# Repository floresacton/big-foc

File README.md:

# big-foc
Field Oriented Control Inverter

70V 160A 10kW continuous

12kW peak

99% efficiency at 8kW

48$ BOM + PCB Cost

65x75x32mm size

Ignoring the heatsink, that's 64kW/L :)

## Design Strategy

### 1. Power and Voltage Rating
- **Power Rating**: Target continuous and peak power
- **Battery Voltage**: 12S = 50.4V, 16S = 67.2V
- **Component Voltage Rating**: Components must be rated at >1.5x-2x battery voltage
  - Example: 16S battery (67.2V max) → 100V+ rated components minimum
  - Margin for voltage spikes, ringing
- **Thermal Limitation**: Max accepted power dissipation at continuous and peak power, <=100C

### 2. Power Stage Design

#### Switch Selection by Voltage
- **Low Voltage (<300V)**: MOSFETs
  - Aim for lower RDS(on) better conduction losses
  - Aim for lower total gate charge for better switching losses
  - Most cost-effective (100V rated components very common)
- **High Voltage (>300V)**: SiC FETs or IGBTs
  - SiC FETs: Fast switching, lower losses
  - IGBTs: Slower switching, higher switching losses, very high power

#### Gate Driver Selection
- **Bootstrap Drivers**: 
  - Simple, low cost
  - Requires minimum duty cycle for bootstrap to charge
  - Usually fine until back emf approaches battery voltage
  - Pick a fast reverse recovery charge diode
  
- **Isolated Drivers**:
  - Independent high-side supply
  - Usually for high-voltage (>300V)
  - Can handle 100% duty cycle
  - Expensive, more complex

### 3. Power Loss Analysis (very important)

#### Switching Losses
- Target switching frequency from 20-25khz (non audible range & less harmonic distortion)
- Transformers and motors are inductive loads (different switching waveforms than resistive switching loss)
- Switching loss ~= 1/2\*switching frequency\*current*voltage\*(t_on+t_off)
- t_on, t_off ~= Q_gate/I_charge
- I_charge = gate drive current

#### Conduction Losses
- I^2*R × rds_on (for mosfets)
- rds_on increases with temperature so we can use parallel FETs without runaway (thermals matter too)

### 4. Current Sensing

#### Sensing Approach
- **Phase count**:
  - Measure 2 phases calculate third (more noise)
  - Measure 3 phases and average (less noise, better if fits & symmetry)

- **In-Phase**:
  - Able to measures phase currents regardless of switch state
  - Higher cost, a lot of common mode noise
  - Better current measurements if done properly
  
- **Low-Side (1-3 shunts)**:
  - Cheaper
  - Simpler ground referenced amplifier design
  - Can only sample during low side conduction
  - Use stm32 timer ADC synchronization

#### Shunt Resistors
 - Should be around or slightly below rds_on of FETs
 - Good to have about 50-75mV at full current
 - Select for 20V/V amplifier (INA181A1 super common & cheap)
 - <=50ppm for 100C temp rise scenario
 - Need amplifier right next to shunt
 - Need center VREF amp for negative and positive current
 - Need to choose settling time to 1% better than 95% duty cycle (bootstrap is limiting factor)

#### Magnetic Sensing
- Hall-effect sensing built in packages
- Galvanic isolation included
- Higher cost, useful for very high currents
- Minimal power dissipation

### 5. Thermals

#### Power Dissipation Calculation
 - On average 2 half bridges are conducting fully, one is not conducting
- total switching loss ~= 4\*single switch loss
- gate charge loss is usually quite small compared to switching and resistive losses for 25khz
- total conduction loss ~= 2\*single conduction loss

#### FET Cooling Orientation
- **Top-Side Cooling**: FETs mounted with drain pad facing up
  - More expensive
  - Easier to cool and route
  
- **Bottom-Side Cooling**: FETs with dissipation through PCB
  - Cheaper
  - Easier assembly
  - Harder low inductance loop

#### Thermal Design Process
1. Calculate junction-to-case thermal resistance (datasheet)
2. Add PCB thermal resistance
3. Add heatsink thermal resistance
4. Junction temp = Ambient + (Total losses \* Total thermal resistance)
5. Target <100C but <60C is better

### 6. Protection and Sensing

#### Temperature Monitoring
- NTC thermistor (cheaper than PTC) on heatsink or FETs
- Lower B kind of better like 3400 because more linear over big range
- 10k 3400B ~= 1k at 100C, 30k at 0C

#### Fast Overvoltage Protection
- Hardware comparator for <1µs response time
- Trigger emergency PWM shutdown (stm32 timer break input)
- Threshold = 0.9% or something of voltage rating
- Directly disables gate drivers
- Optional avalanche diode for last resort protection

#### Voltage Measurement
- Resistor divider to ADC with a little bit of filtering
- Per-phase voltage for locking onto back emf for high speed

### 7. Microcontroller Selection

#### STM32G4 Series
**Key Features for FOC:**
- High-resolution timers with dead-time insertion and center aligned PWM
- Fast 12-bit ADCs
- ADC triggering synchronized to PWM for current sampling
- Multiple ADCs for simultaneous phase current sampling
- Math acceleration (FPU, CORDIC) for FOC
- Sufficient for >20kHz control loop

**Typical MCU Choices:**
- STM32G431: Small packages, cost-optimized
- STM32G474: More peripherals, flash, and RAM for complex algorithms

### 8. FOC Control Implementation

#### Control Loop Structure
- Current loop: 10-50kHz (1/10 of switching frequency typical)
- Velocity loop: 1-5kHz
- Position loop: 100-1000Hz

#### Key Considerations
- ADC sampling synchronized to PWM valley/center
- Current reconstruction for low-side shunts
- PI controller tuning based on motor parameters
- Clarke/Park transforms for coordinate conversion
- Space Vector Modulation (SVM) for efficient bus utilization
- Add third harmonic for higher effective bus voltage

### 9. PCB Layout (Very very important)
 - Low inductance switching loop
 - di/dt \* L = voltage induced over drain source
 - Low esr (usually MLCC) caps in low inductance switching loop
 - very rough calc Q_sustain = t_deadtime*I_peak
 - Q_sustain / V_spike = C_switch loop
 - Goal to hit V_spike <1% of V_bus
 - Keep loops as small as possible
 - Shunt amplifier right next to shunt resistor

### 10. Connectors
 - Waterproof, either SD13 series or DT Duetch (orange ones) are common
 - Phase and power wires just shrouded, bolt internally

### 11. Example Calculations (for my inverter)
- **Motor Characteristics**
	- 40uH phase to phase inductance
	- AMKs have 2.5nF inter winding capacitance
	- Couldn't find inter-winding capacitance of mine, but I think its relatively small losses compared to conduction
- [MOSFET loss equations](https://www.ti.com/lit/an/slyt664/slyt664.pdf?ts=1762657470589)
- [Layout and more equations](https://www.infineon.com/assets/row/public/documents/24/42/infineon-designing-an-optimized-half-bridge-dc-dc-converter-with-medium-voltage-coolgan-transistors-applicationnotes-en.pdf)
 - **Losses**
	 - Power 8.4kW at 120A rms current or two phases at 170A
	 - 2 phases on at a time on average (same thing as 3 RMS currents)
	 - parallel rds @ 15V: 0.55mohm at 25C, 0.85mohm at 100C
	 - P_cond_tot = 2\*170\*170\*0.00055 = 32W
	 - P_shunt = 2\*170\*170\*0.00033 = 19W
	 - Q_gs2 = 20nC, Q_gd = 50nC, Q_eff = 70nC
	 - Q_actual = 140nC cause parallel FETs
	 - P_sw = 2\*70V\*170A\*25khz\*140nC/4A = 20.8W
	 - P_sw_total = 8.925W\*2 half bridge = 41.6W
     - P_recovery = 25khz\*200nC\*70V*8FETs = 2.8W
	 - P_coss = 12FETs \* 25khz \* 70V^2 \* 2.3nF = 3.4W
	 - P_winding_cap = 3 phase \* 25khz \* 70V^2 \* 2.5nF = 0.9W
	 - P_gate_total = 12 FETs\*250nC\*15V\*25khz = 1.1W
	 - P_gate_drive = <1W
	 - Deadtime 150ns
	 - P_diode = ~1.5\*1.2V\*170A\*25khz\*150ns = 1.2W (a bit sus math but reasonable)
	 - 4% dissipation factor for 1206 2.2uF ~ 10mohm I think for equivalent 10 (randomish number)
	 - Sw_energy = 70V\*170A\*140nC/4A = 0.4mJ per phase
	 - C_droop ~= 0.4mJ/(20uF \* 70V) = 0.3V
	 - The Vrms of the droop is prob below ~50mV
	 - P_cap_sw = 50mV^2/10mohm = 0.25W*3phases comes to <1W
	 - I_ripple ~= 110A
	 - Assuming 70A into ceramics and 40A into electrolytic
	 - 80 ceramics / 70A = 0.87A per ceramic
	 - P_ripple_cer = 0.875^2 \* 100mohm = 80mW
	 - P_cer_tot = 0.08*80 = 6.4W
	 - Electrolytic 3mohm at 25khz (susish think ok)
	 - I_elec ~= 40A/10 = 4A
	 - P_elec = 4A^2 \* 3mohm = 48mW
	 - P_elec_tot = 48mW \* 10 = 0.5W
	 - Total at 8.4kW = 32+41.6+1.1+1.2+1+1+6.4+0.5+3.4+19+2.8= 109.9W
	 - About 98.6% efficiency
- **Control**
	- Max phase current 220A, 210A max (170rms) is 12kW
	- SVPWM
	- Optional 3rd harmonic overmodulation
	- I_phase_rms = I_phase_pk / sqrt(12)
	- I_pk_pk_ripple = 70V / (2 \* 40uH \* 25khz) \* D \* (1-D) = 8.75A ; D=0.5
	- I_pk = 4.4A
	- I_rms = I_pk_pk_ripple / sqrt(12) = 2.5A

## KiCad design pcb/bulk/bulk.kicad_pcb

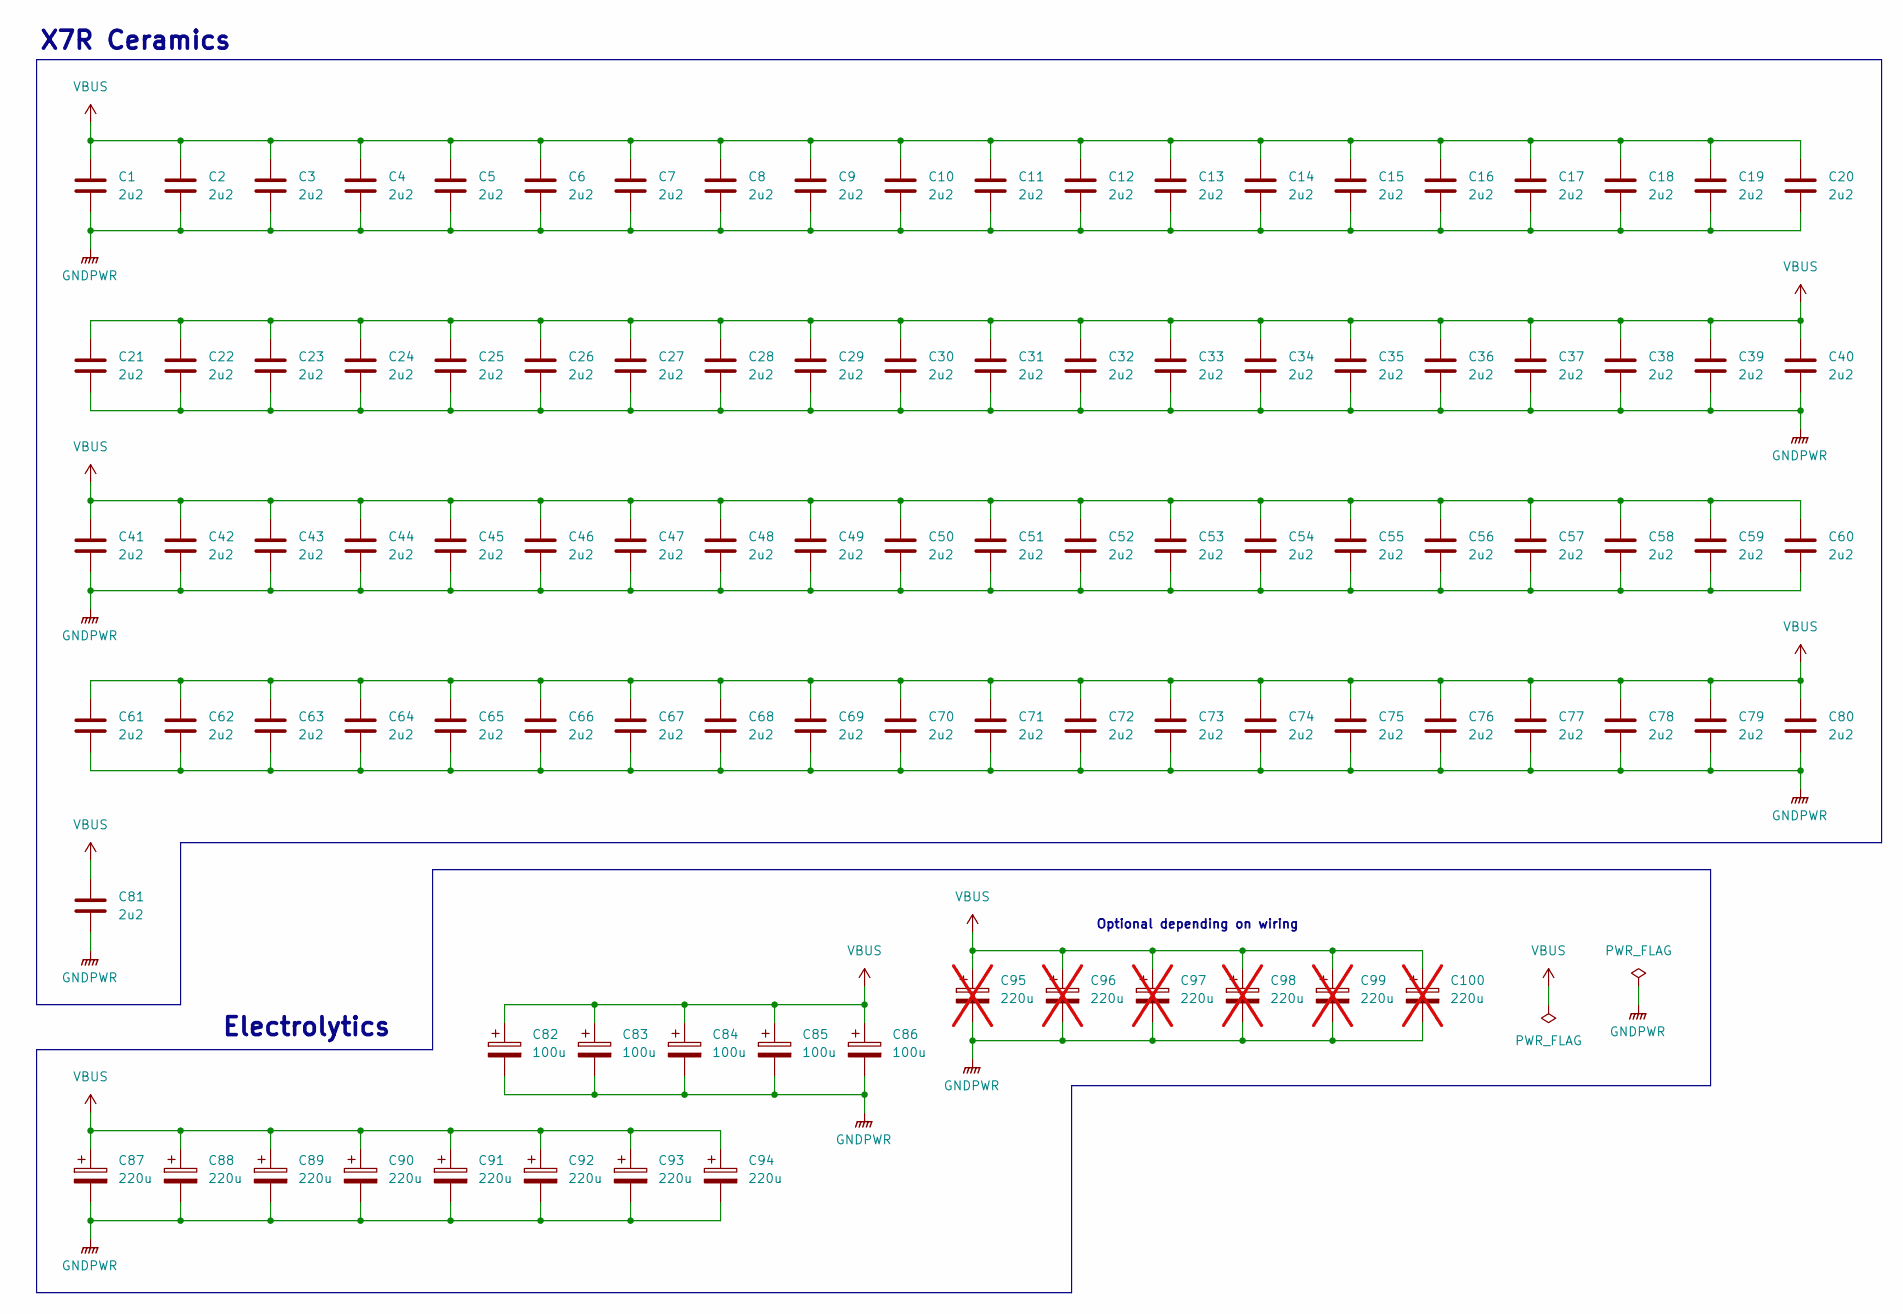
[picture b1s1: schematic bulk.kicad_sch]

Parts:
C1, C2, C3, C4, C5, C6, C7, C8, C9, C10, C11, C12, C13, C14, C15, C16, C17, C18, C19, C20, C21, C22, C23, C24, C25, C26, C27, C28, C29, C30, C31, C32, C33, C34, C35, C36, C37, C38, C39, C40, C41, C42, C43, C44, C45, C46, C47, C48, C49, C50, C51, C52, C53, C54, C55, C56, C57, C58, C59, C60, C61, C62, C63, C64, C65, C66, C67, C68, C69, C70, C71, C72, C73, C74, C75, C76, C77, C78, C79, C80, C81: 2u2; C_1206_3216Metric; LCSC C920964
C82, C83, C84, C85, C86: 100u; C_Radial_D10.0mm_H20.0mm_P5.00mm; LCSC C106541
C87, C88, C89, C90, C91, C92, C93, C94: 220u; C_Radial_D12.5mm_H20.0mm_P5.00mm; LCSC C5213780
C95, C96, C97, C98, C99, C100: 220u; C_Radial_D12.5mm_H20.0mm_P5.00mm; LCSC C5213780; not fitted

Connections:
GNDPWR: C1.2, C2.2, C3.2, C4.2, C5.2, C6.2, C7.2, C8.2, C9.2, C10.2, C11.2, C12.2, C13.2, C14.2, C15.2, C16.2, C17.2, C18.2, C19.2, C20.2, C21.2, C22.2, C23.2, C24.2, C25.2, C26.2, C27.2, C28.2, C29.2, C30.2, C31.2, C32.2, C33.2, C34.2, C35.2, C36.2, C37.2, C38.2, C39.2, C40.2, C41.2, C42.2, C43.2, C44.2, C45.2, C46.2, C47.2, C48.2, C49.2, C50.2, C51.2, C52.2, C53.2, C54.2, C55.2, C56.2, C57.2, C58.2, C59.2, C60.2, C61.2, C62.2, C63.2, C64.2, C65.2, C66.2, C67.2, C68.2, C69.2, C70.2, C71.2, C72.2, C73.2, C74.2, C75.2, C76.2, C77.2, C78.2, C79.2, C80.2, C81.2, C82.2, C83.2, C84.2, C85.2, C86.2, C87.2, C88.2, C89.2, C90.2, C91.2, C92.2, C93.2, C94.2, C95.2, C96.2, C97.2, C98.2, C99.2, C100.2
VBUS: C1.1, C2.1, C3.1, C4.1, C5.1, C6.1, C7.1, C8.1, C9.1, C10.1, C11.1, C12.1, C13.1, C14.1, C15.1, C16.1, C17.1, C18.1, C19.1, C20.1, C21.1, C22.1, C23.1, C24.1, C25.1, C26.1, C27.1, C28.1, C29.1, C30.1, C31.1, C32.1, C33.1, C34.1, C35.1, C36.1, C37.1, C38.1, C39.1, C40.1, C41.1, C42.1, C43.1, C44.1, C45.1, C46.1, C47.1, C48.1, C49.1, C50.1, C51.1, C52.1, C53.1, C54.1, C55.1, C56.1, C57.1, C58.1, C59.1, C60.1, C61.1, C62.1, C63.1, C64.1, C65.1, C66.1, C67.1, C68.1, C69.1, C70.1, C71.1, C72.1, C73.1, C74.1, C75.1, C76.1, C77.1, C78.1, C79.1, C80.1, C81.1, C82.1, C83.1, C84.1, C85.1, C86.1, C87.1, C88.1, C89.1, C90.1, C91.1, C92.1, C93.1, C94.1, C95.1, C96.1, C97.1, C98.1, C99.1, C100.1

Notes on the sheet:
X7R Ceramics
Optional depending on wiring
Electrolytics

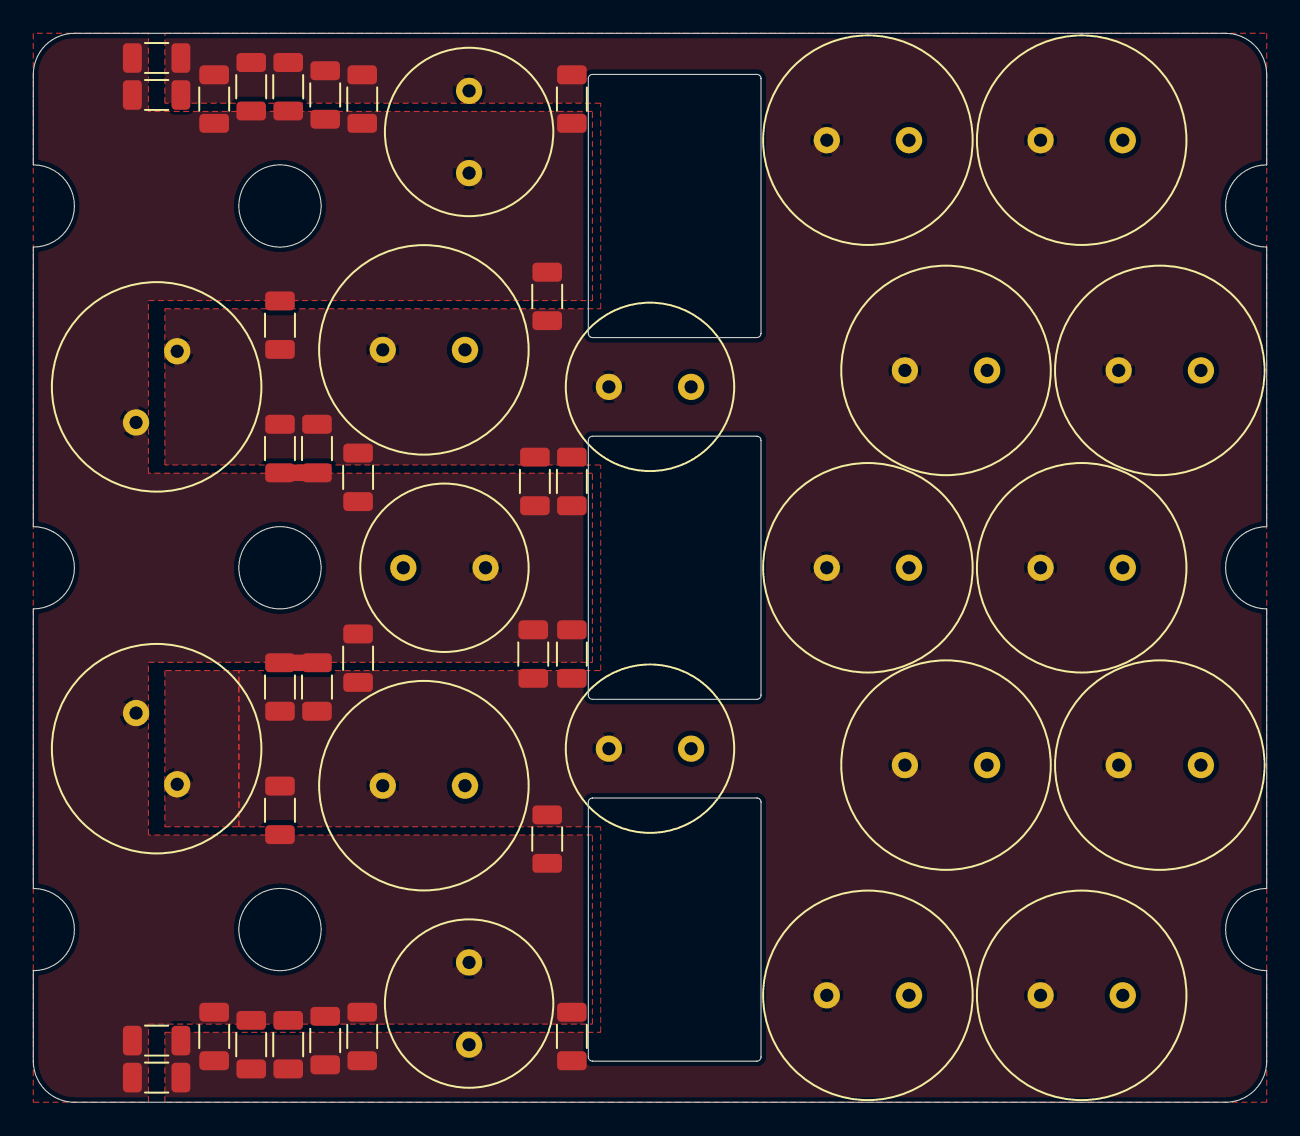
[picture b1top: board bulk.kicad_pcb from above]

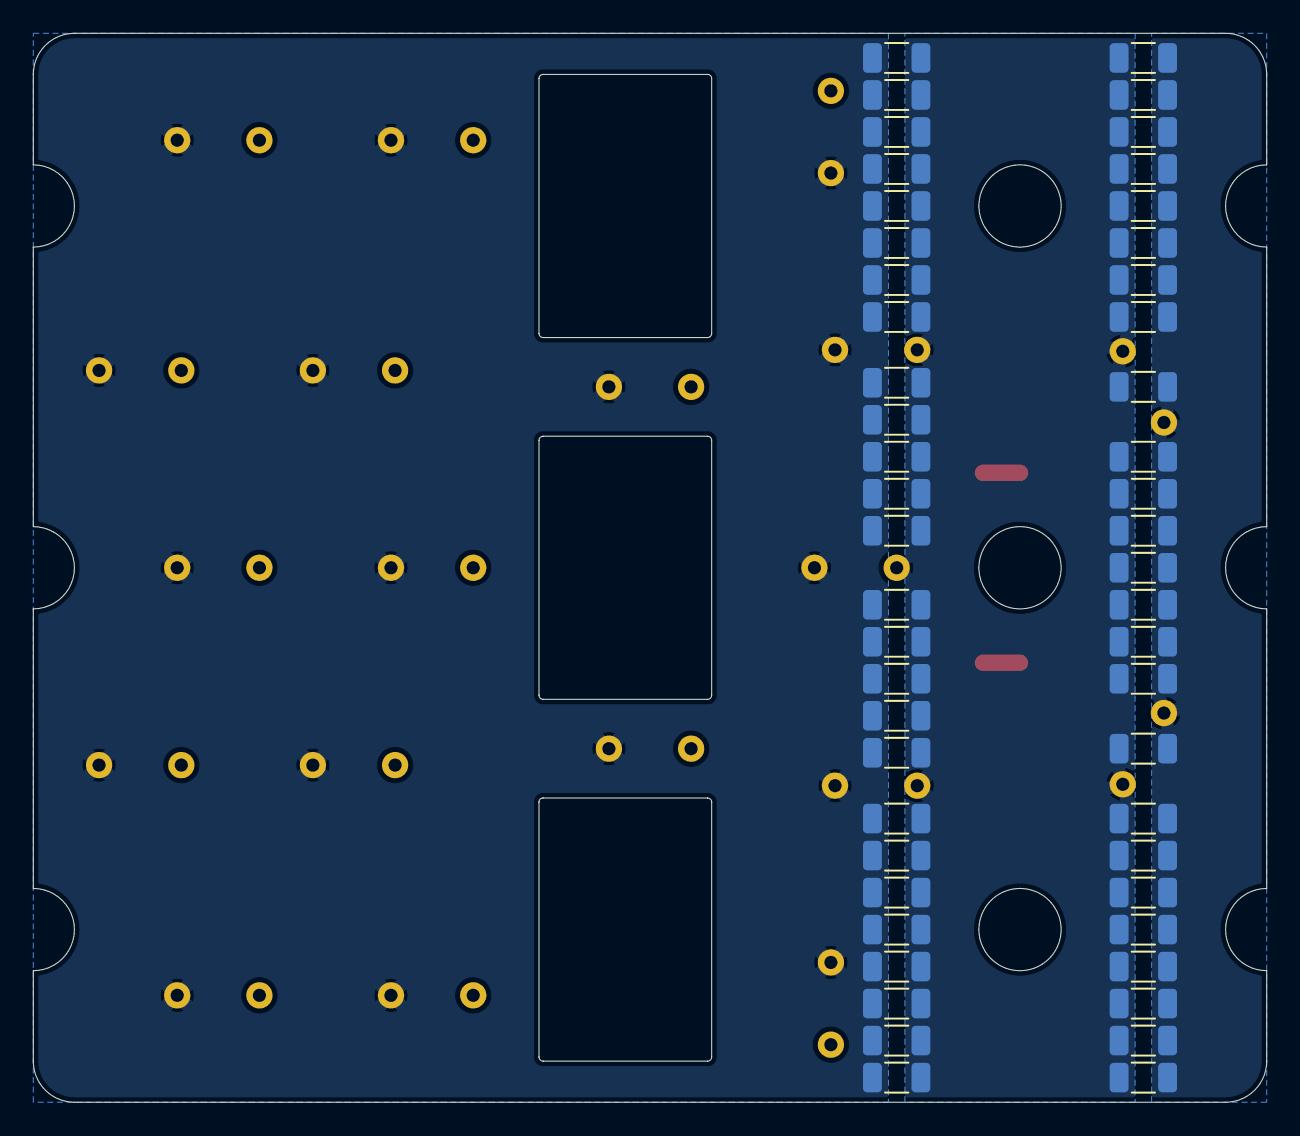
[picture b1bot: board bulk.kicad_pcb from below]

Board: 2 copper layers, 75.0 x 65.0 mm, 100 parts (51 on the bottom side), 2 nets.

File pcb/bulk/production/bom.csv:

Designator,Footprint,Quantity,Value,LCSC Part #
"C1, C10, C11, C12, C13, C14, C15, C16, C17, C18, C19, C2, C20, C21, C22, C23, C24, C25, C26, C27, C28, C29, C3, C30, C31, C32, C33, C34, C35, C36, C37, C38, C39, C4, C40, C41, C42, C43, C44, C45, C46, C47, C48, C49, C5, C50, C51, C52, C53, C54, C55, C56, C57, C58, C59, C6, C60, C61, C62, C63, C64, C65, C66, C67, C68, C69, C7, C70, C71, C72, C73, C74, C75, C76, C77, C78, C79, C8, C80, C81, C9",1206,81,2u2,C920964
"C82, C83, C84, C85, C86",C_Radial_D10.0mm_H20.0mm_P5.00mm,5,100u,C106541
"C87, C88, C89, C90, C91, C92, C93, C94",C_Radial_D12.5mm_H20.0mm_P5.00mm,8,220u,C5213780

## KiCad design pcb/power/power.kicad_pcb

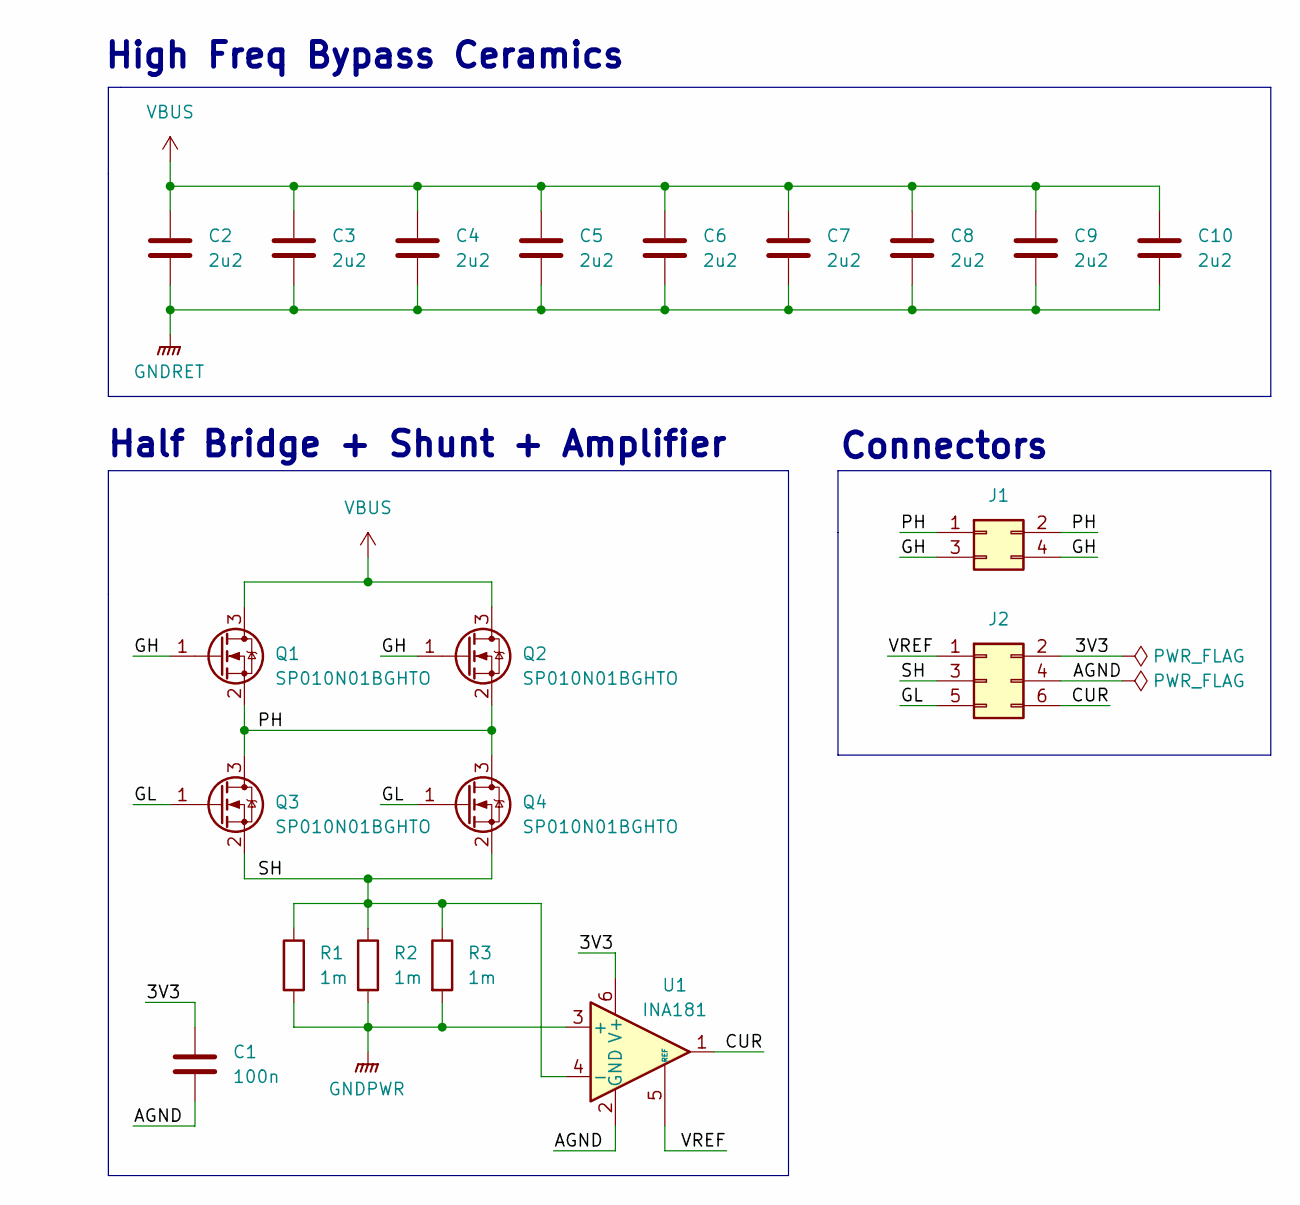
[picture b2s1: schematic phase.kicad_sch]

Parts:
C1: 100n; C_0402_1005Metric; LCSC C307331
C2, C3, C4, C5, C6, C7, C8, C9, C10: 2u2; C_1206_3216Metric; LCSC C920964
J1: Conn_02x02_Odd_Even; PinHeader_2x02_P1.27mm_Vertical_SMD; LCSC C27985143
J2: Conn_02x03_Odd_Even; PinHeader_2x03_P1.27mm_Vertical_SMD; LCSC C27985144
Q1, Q2, Q3, Q4: SP010N01BGHTO; Infineon_PG-HSOF-8-1; LCSC C22385350
R1, R2, R3: 1m; R_Shunt_3921; LCSC C2927603
U1: INA181; SOT-23-6; LCSC C52097916

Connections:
/Phase1/3V3: C1.1, J2.2, U1.6 (V+)
/Phase1/AGND: C1.2, J2.4, U1.2 (GND)
/Phase1/CUR: J2.6, U1.1
/Phase1/GH: J1.3, J1.4, Q1.1 (G), Q2.1 (G)
/Phase1/GL: J2.5, Q3.1 (G), Q4.1 (G)
/Phase1/PH: J1.1, J1.2, Q1.2 (S), Q2.2 (S), Q3.3 (D), Q4.3 (D)
/Phase1/SH: J2.3, Q3.2 (S), Q4.2 (S), R1.1, R2.1, R3.1, U1.4 (-)
/Phase1/VREF: J2.1, U1.5 (REF)
GNDPWR: R1.2, R2.2, R3.2, U1.3 (+); also elsewhere on the board
GNDRET: C2.2, C3.2, C4.2, C5.2, C6.2, C7.2, C8.2, C9.2, C10.2; also elsewhere on the board
VBUS: C2.1, C3.1, C4.1, C5.1, C6.1, C7.1, C8.1, C9.1, C10.1, Q1.3 (D), Q2.3 (D); also elsewhere on the board

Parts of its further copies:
C11, C21: 100n; C_0402_1005Metric; LCSC C307331
C12, C13, C14, C15, C16, C17, C18, C19, C20, C22, C23, C24, C25, C26, C27, C28, C29, C30: 2u2; C_1206_3216Metric; LCSC C920964
J3, J5: Conn_02x02_Odd_Even; PinHeader_2x02_P1.27mm_Vertical_SMD; LCSC C27985143
J4, J6: Conn_02x03_Odd_Even; PinHeader_2x03_P1.27mm_Vertical_SMD; LCSC C27985144
Q5, Q6, Q7, Q8, Q9, Q10, Q11, Q12: SP010N01BGHTO; Infineon_PG-HSOF-8-1; LCSC C22385350
R4, R5, R6, R7, R8, R9: 1m; R_Shunt_3921; LCSC C2927603
U2, U3: INA181; SOT-23-6; LCSC C52097916

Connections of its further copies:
/Phase2/3V3: C11.1, J4.2, U2.6 (V+)
/Phase2/AGND: C11.2, J4.4, U2.2 (GND)
/Phase2/CUR: J4.6, U2.1
/Phase2/GH: J3.3, J3.4, Q5.1 (G), Q6.1 (G)
/Phase2/GL: J4.5, Q7.1 (G), Q8.1 (G)
/Phase2/PH: J3.1, J3.2, Q5.2 (S), Q6.2 (S), Q7.3 (D), Q8.3 (D)
/Phase2/SH: J4.3, Q7.2 (S), Q8.2 (S), R4.1, R5.1, R6.1, U2.4 (-)
/Phase2/VREF: J4.1, U2.5 (REF)
/Phase3/3V3: C21.1, J6.2, U3.6 (V+)
/Phase3/AGND: C21.2, J6.4, U3.2 (GND)
/Phase3/CUR: J6.6, U3.1
/Phase3/GH: J5.3, J5.4, Q9.1 (G), Q10.1 (G)
/Phase3/GL: J6.5, Q11.1 (G), Q12.1 (G)
/Phase3/PH: J5.1, J5.2, Q9.2 (S), Q10.2 (S), Q11.3 (D), Q12.3 (D)
/Phase3/SH: J6.3, Q11.2 (S), Q12.2 (S), R7.1, R8.1, R9.1, U3.4 (-)
/Phase3/VREF: J6.1, U3.5 (REF)
GNDPWR: R4.2, R5.2, R6.2, R7.2, R8.2, R9.2, U2.3 (+), U3.3 (+); also elsewhere on the board
GNDRET: C12.2, C13.2, C14.2, C15.2, C16.2, C17.2, C18.2, C19.2, C20.2, C22.2, C23.2, C24.2, C25.2, C26.2, C27.2, C28.2, C29.2, C30.2; also elsewhere on the board
VBUS: C12.1, C13.1, C14.1, C15.1, C16.1, C17.1, C18.1, C19.1, C20.1, C22.1, C23.1, C24.1, C25.1, C26.1, C27.1, C28.1, C29.1, C30.1, Q5.3 (D), Q6.3 (D), Q9.3 (D), Q10.3 (D); also elsewhere on the board

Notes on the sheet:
High Freq Bypass Ceramics
Connectors
Half Bridge + Shunt + Amplifier

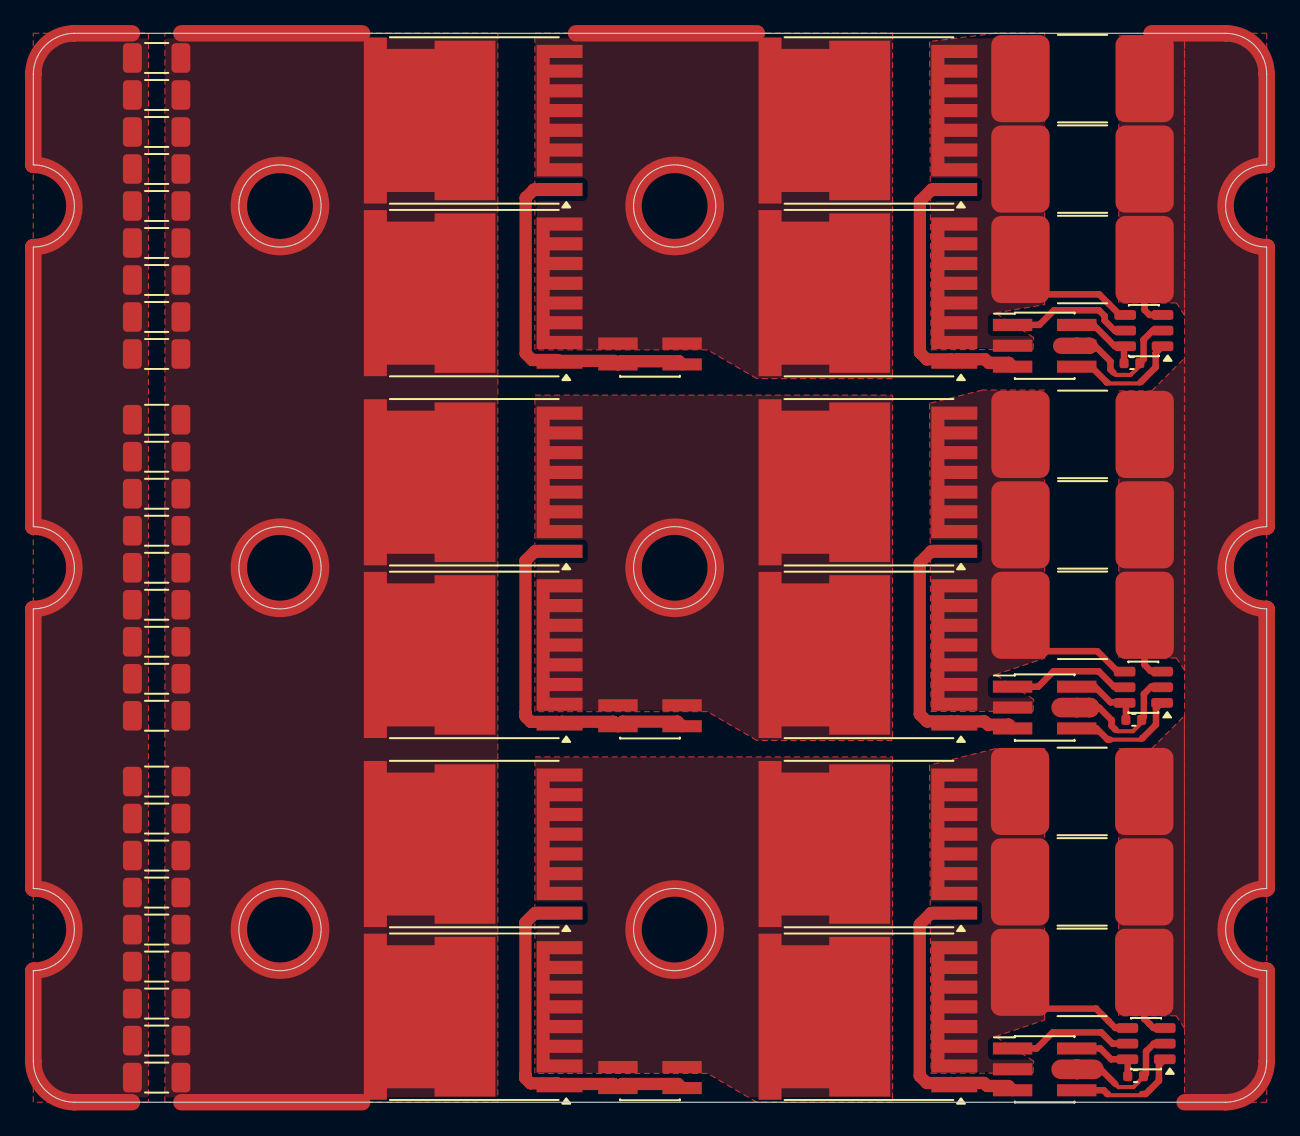
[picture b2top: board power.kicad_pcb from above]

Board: 2 copper layers, 75.0 x 65.0 mm, 60 parts (0 on the bottom side), 27 nets.

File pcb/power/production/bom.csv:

Designator,Footprint,Quantity,Value,LCSC Part #
"C1, C11, C21",0402,3,100n,C1525
"C10, C12, C13, C14, C15, C16, C17, C18, C19, C2, C20, C22, C23, C24, C25, C26, C27, C28, C29, C3, C30, C4, C5, C6, C7, C8, C9",1206,27,2u2,C920964
"J1, J3, J5",PinHeader_2x02_P1.27mm_Vertical_SMD,3,Conn_02x02_Odd_Even,C27985143
"J2, J4, J6",PinHeader_2x03_P1.27mm_Vertical_SMD,3,Conn_02x03_Odd_Even,C27985144
"Q1, Q10, Q11, Q12, Q2, Q3, Q4, Q5, Q6, Q7, Q8, Q9",Infineon_PG-HSOF-8-1,12,SP010N01BGHTO,C22385350
"R1, R2, R3, R4, R5, R6, R7, R8, R9",R_Shunt_3921,9,1m,C2927603
"U1, U2, U3",SOT-23-6,3,INA181,C52097916

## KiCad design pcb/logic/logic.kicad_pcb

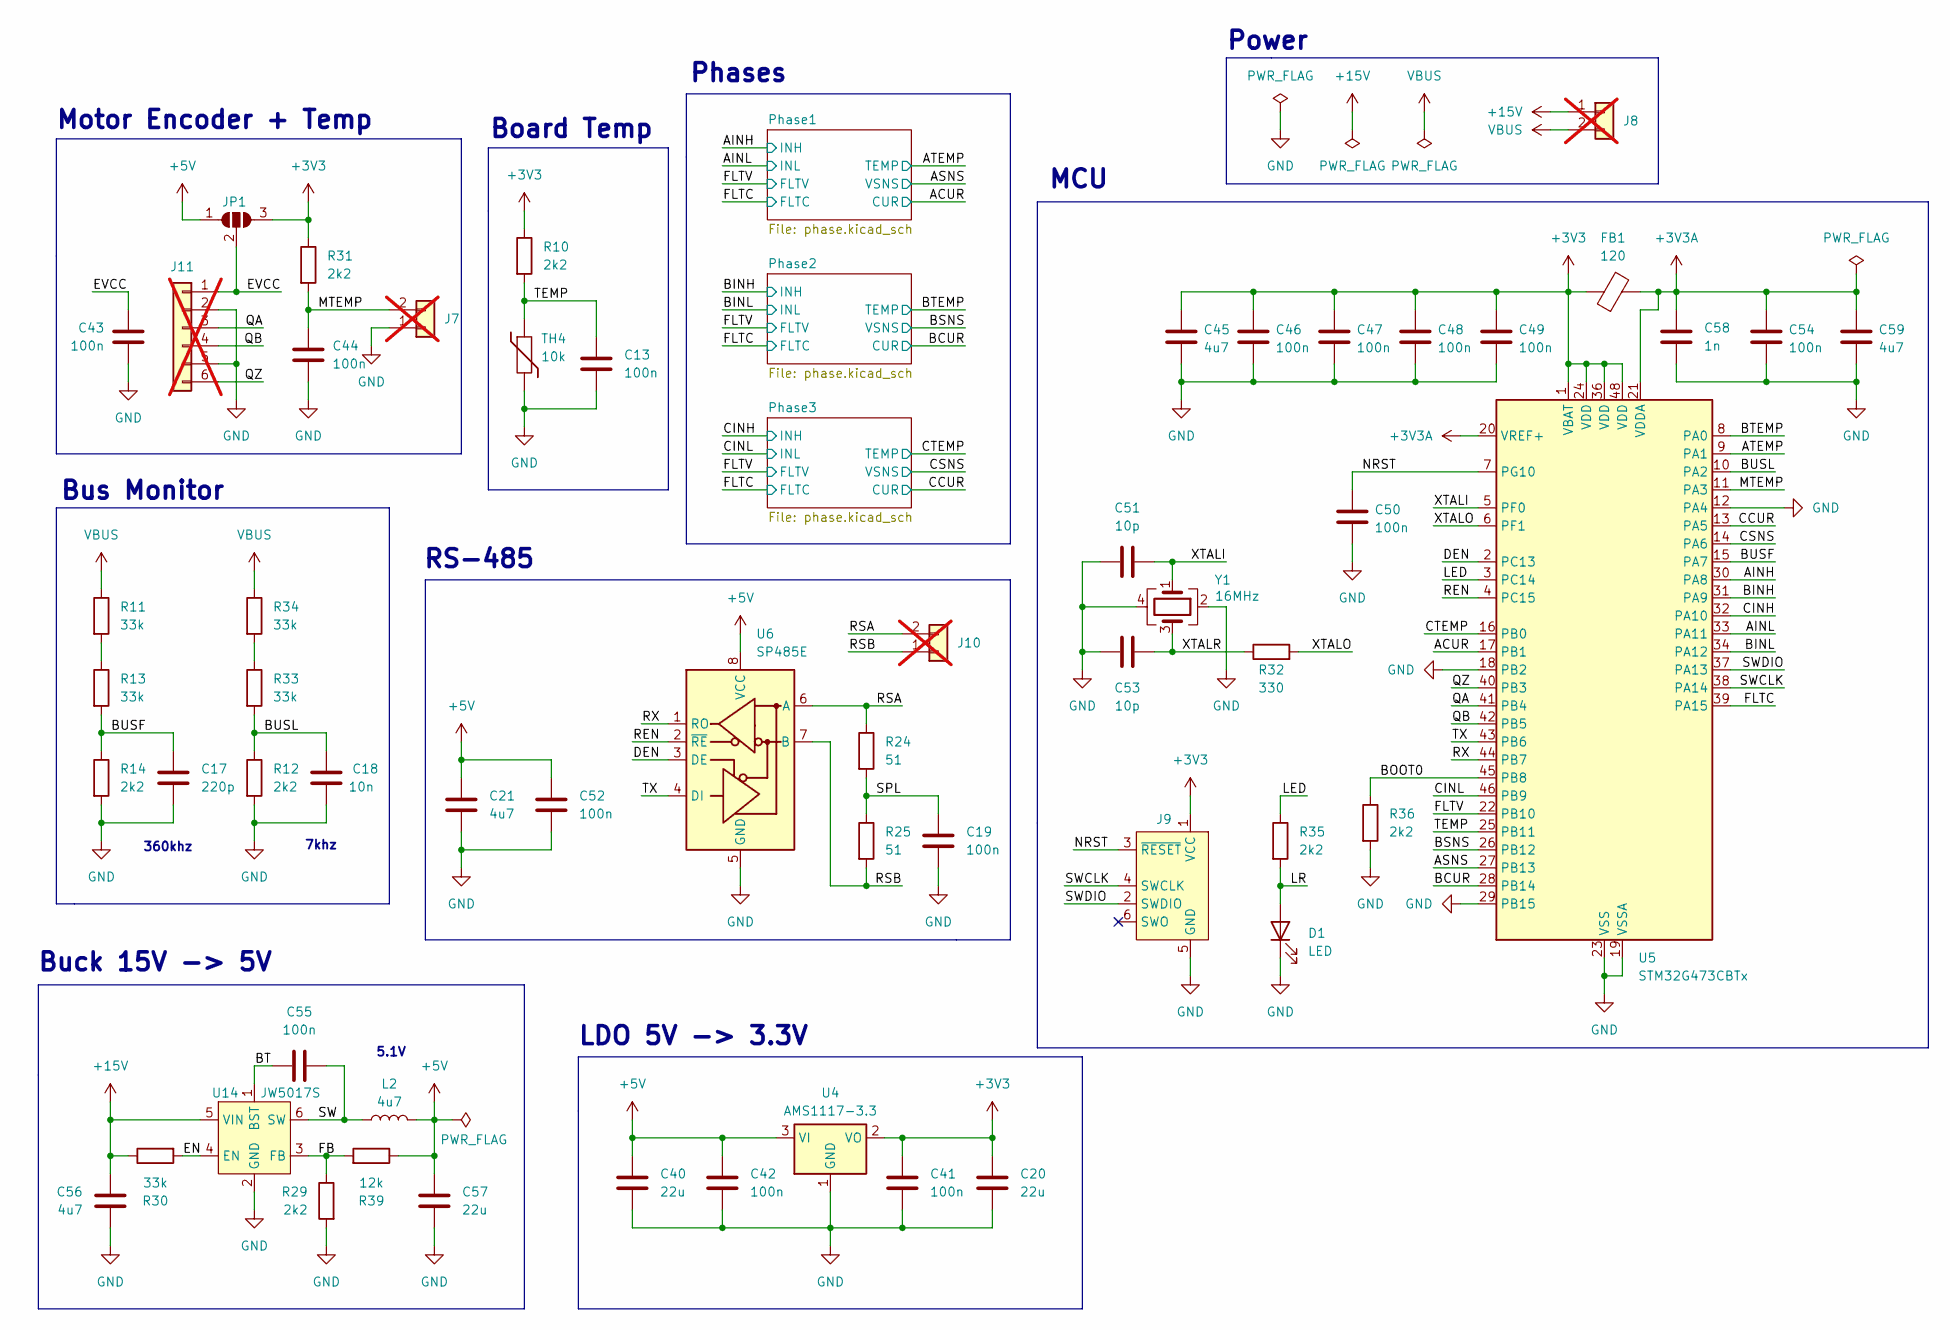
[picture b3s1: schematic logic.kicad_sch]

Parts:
C13, C19, C41, C42, C43, C44, C46, C47, C48, C49, C50, C52, C54, C55: 100n; C_0402_1005Metric; LCSC C307331
C17: 220p; C_0402_1005Metric; LCSC C1530
C18: 10n; C_0402_1005Metric; LCSC C15195
C20, C40, C57: 22u; C_1206_3216Metric; LCSC C20416445
C21, C45, C56, C59: 4u7; C_0805_2012Metric; LCSC C33546011
C51, C53: 10p; C_0402_1005Metric; LCSC C32949
C58: 1n; C_0402_1005Metric; LCSC C1523
D1: LED; LED_0603_1608Metric; LCSC C2290
FB1: 120; L_0603_1608Metric; LCSC C14709
J7, J8, J10: Conn_01x02; 1x02_2.00mm_Solder; not fitted
J9: Conn_ARM_SWD_TagConnect_TC2030-NL; Tag-Connect_TC2030-IDC-NL_2x03_P1.27mm_Vertical
J11: Conn_01x06; 1x06_2.00mm_Solder; not fitted
JP1: SolderJumper_3_Open; SolderJumper-3_P1.3mm_Open_RoundedPad1.0x1.5mm
L2: 4u7; L_TechFuse_SL0420; LCSC C22463808
R10, R12, R14, R29, R31, R35, R36: 2k2; R_0402_1005Metric; LCSC C25879
R11, R13, R30, R33, R34: 33k; R_0402_1005Metric; LCSC C25779
R24, R25: 51; R_0805_2012Metric; LCSC C17738
R32: 330; R_0402_1005Metric; LCSC C25104
R39: 12k; R_0402_1005Metric; LCSC C25752
TH4: 10k; R_0402_1005Metric; LCSC C41417281
U4: AMS1117-3.3; SOT-223-3_TabPin2; LCSC C6186
U5: STM32G473CBTx; LQFP-48_7x7mm_P0.5mm; LCSC C730111
U6: SP485E; JEITA_SOIC-8_3.9x4.9mm_P1.27mm; LCSC C6855
U14: JW5017S; SOT-23-6; LCSC C371172
Y1: 16MHz; Crystal_SMD_3225-4Pin_3.2x2.5mm; LCSC C13738

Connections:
+3V3: C20.1, C41.1, C45.1, C46.1, C47.1, C48.1, C49.1, FB1.1, J9.1 (VCC), JP1.3 (B), R10.1, R31.1, U4.2 (VO), U5.1 (VBAT), U5.24 (VDD), U5.36 (VDD), U5.48 (VDD); also elsewhere on the board
+3V3A: C54.1, C58.1, C59.1, FB1.2, U5.20 (VREF+), U5.21 (VDDA)
+5V: C21.1, C40.1, C42.1, C52.1, C57.1, JP1.1 (A), L2.2, R39.1, U4.3 (VI), U6.8 (VCC)
+15V: C56.1, J8.1, R30.1, U14.5 (VIN); also elsewhere on the board
/ACUR: U5.17 (PB1); also elsewhere on the board
/AINH: U5.30 (PA8); also elsewhere on the board
/AINL: U5.33 (PA11); also elsewhere on the board
/ASNS: U5.27 (PB13); also elsewhere on the board
/ATEMP: U5.9 (PA1); also elsewhere on the board
/BCUR: U5.28 (PB14); also elsewhere on the board
/BINH: U5.31 (PA9); also elsewhere on the board
/BINL: U5.34 (PA12); also elsewhere on the board
/BOOT0: R36.1, U5.45 (PB8)
/BSNS: U5.26 (PB12); also elsewhere on the board
/BT: C55.1, U14.1 (BST)
/BTEMP: U5.8 (PA0); also elsewhere on the board
/BUSF: C17.1, R13.2, R14.1, U5.15 (PA7)
/BUSL: C18.1, R12.1, R33.2, U5.10 (PA2)
/CCUR: U5.13 (PA5); also elsewhere on the board
/CINH: U5.32 (PA10); also elsewhere on the board
/CINL: U5.46 (PB9); also elsewhere on the board
/CSNS: U5.14 (PA6); also elsewhere on the board
/CTEMP: U5.16 (PB0); also elsewhere on the board
/DEN: U5.2 (PC13), U6.3 (DE)
/EN: R30.2, U14.4 (EN)
/EVCC: C43.1, J11.1, JP1.2 (C)
/FB: R29.1, R39.2, U14.3 (FB)
/FLTC: U5.39 (PA15); also elsewhere on the board
/FLTV: U5.22 (PB10); also elsewhere on the board
/LED: R35.1, U5.3 (PC14)
/LR: D1.2 (A), R35.2
/MTEMP: C44.1, J7.2, R31.2, U5.11 (PA3)
/NRST: C50.1, J9.3 (~RESET), U5.7 (PG10)
/QA: J11.3, U5.41 (PB4)
/QB: J11.4, U5.42 (PB5)
/QZ: J11.6, U5.40 (PB3)
/REN: U5.4 (PC15), U6.2 (~RE)
/RSA: J10.2, R24.1, U6.6 (A)
/RSB: J10.1, R25.2, U6.7 (B)
/RX: U5.44 (PB7), U6.1 (RO)
/SPL: C19.2, R24.2, R25.1
/SW: C55.2, L2.1, U14.6 (SW)
/SWCLK: J9.4 (SWCLK), U5.38 (PA14)
/SWDIO: J9.2 (SWDIO), U5.37 (PA13)
/TEMP: C13.1, R10.2, TH4.1, U5.25 (PB11)
/TX: U5.43 (PB6), U6.4 (DI)
/XTALI: C51.2, U5.5 (PF0), Y1.1
/XTALO: R32.2, U5.6 (PF1)
/XTALR: C53.2, R32.1, Y1.3
GND: C13.2, C17.2, C18.2, C19.1, C20.2, C21.2, C40.2, C41.2, C42.2, C43.2, C44.2, C45.2, C46.2, C47.2, C48.2, C49.2, C50.2, C51.1, C52.2, C53.1, C54.2, C56.2, C57.2, C58.2, C59.2, D1.1 (K), J7.1, J9.5 (GND), J11.2, J11.5, R12.2, R14.2, R29.2, R36.2, TH4.2, U4.1 (GND), U5.12 (PA4), U5.18 (PB2), U5.19 (VSSA), U5.23 (VSS), U5.29 (PB15), U5.35 (VSS), U5.47 (VSS), U6.5 (GND), U14.2 (GND), Y1.2, Y1.4; also elsewhere on the board
unnamed: R11.2, R13.1
unnamed: R33.1, R34.2
VBUS: J8.2, R11.1, R34.1

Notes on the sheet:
Board Temp
Power
Motor Encoder + Temp
5.1V
LDO 5V -> 3.3V
Bus Monitor
RS-485
360khz
Phases
MCU
7khz
Buck 15V -> 5V
